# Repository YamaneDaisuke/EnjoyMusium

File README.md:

# EnjoyMusium
エンジョイ科学館で使用するプログラムや文書用リポジトリ

## フォルダ構成
 - **IR_Controller**
   赤外信号学習コントローラ用フォルダ
   - documents
   - PCB
   - programs
     - LPC1114 (LPC1114FN用プログラム 開発環境: mbedオンラインIDE)
     - PIC16F690.X  (PIC16F690用プログラム 開発環境: MPLAB X IDE)
 
 - **SpeechSynthesisWriter**
   音声合成回路用フォルダ
   - documents
   - PCB
   - programs
    - lpc1114fn (LPC1114FN用プログラム 開発環境: mbedオンラインIDE)
    - SetUp (インストーラ用プロジェクト 開発環境: visual studiio2015)
    - SpeechSynthesisWriter_CS (書き込みツール用プロジェクト 開発環境: visual studiio2015)

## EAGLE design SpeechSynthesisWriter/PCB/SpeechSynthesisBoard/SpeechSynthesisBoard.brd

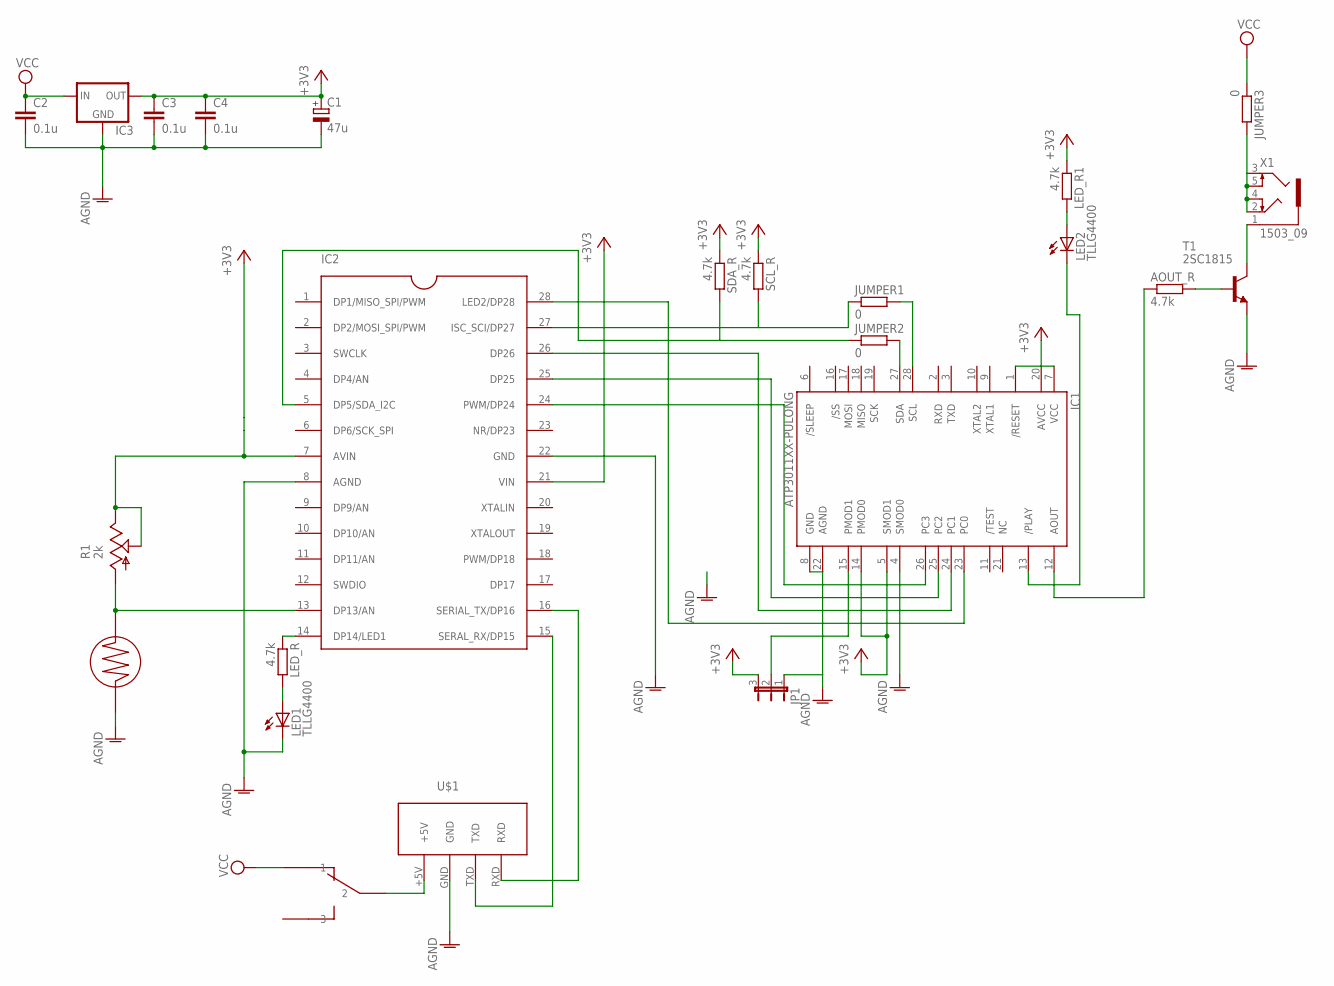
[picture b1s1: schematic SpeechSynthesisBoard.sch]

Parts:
AOUT_R: 4.7k; 0204/7
B-12JB1: B-12JV
C1: 47u; E2,5-5
C2, C3, C4: 0.1u; C025-024X044
CDS_5MM1: CDS_5MM
IC1: ATP3011XX-PULONG; DIL28-3
IC2: LPC1114FN28; DIP28
IC3: 78XXL
JP1: JP2E; JP2
JUMPER1, JUMPER2, JUMPER3: 0; 0309/12
LED1, LED2: TLLG4400; LED3MM
LED_R, LED_R1: 4.7k; 0204/7
R1: 2k; CA6V
SCL_R: 4.7k; 0204/7
SDA_R: 4.7k; 0204/7
T1: 2SC1815; TO92-ECB
U$1: USB2UART
X1: 1503_09

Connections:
+3V3: C1.+, C3.1, C4.1, IC1.1 (/RESET), IC1.5 (SMOD1), IC1.7 (VCC), IC1.14 (PMOD0), IC1.20 (AVCC), IC2.7 (AVIN), IC2.21 (VIN), IC3.OUT, JP1.3, LED_R1.1, R1.E, R1.S, SCL_R.1, SDA_R.1
AGND: C1.-, C2.2, C3.2, C4.2, CDS_5MM1.P$2, IC1.4 (SMOD0), IC1.8 (GND), IC1.22 (AGND), IC2.8 (AGND), IC2.22 (GND), IC3.GND, JP1.1, LED1.K (C), T1.E, U$1.GND
unnamed: LED1.A, LED_R.2
unnamed: IC1.13 (/PLAY), LED2.K (C)
unnamed: IC2.14 (DP14/LED1), LED_R.1
unnamed: LED2.A, LED_R1.2
unnamed: AOUT_R.1, IC1.12 (AOUT)
unnamed: AOUT_R.2, T1.B
unnamed: IC2.27 (ISC_SCI/DP27), JUMPER1.1, SCL_R.2
unnamed: IC2.5 (DP5/SDA_I2C), JUMPER2.1, SDA_R.2
unnamed: T1.C, X1.1
unnamed: IC1.26 (PC3), IC2.24 (PWM/DP24)
unnamed: IC1.25 (PC2), IC2.25 (DP25)
unnamed: IC1.23 (PC0), IC2.28 (LED2/DP28)
unnamed: IC1.24 (PC1), IC2.26 (DP26)
unnamed: IC2.16 (SERIAL_TX/DP16), U$1.RXD
unnamed: IC1.15 (PMOD1), JP1.2
unnamed: IC2.15 (SERAL_RX/DP15), U$1.TXD
unnamed: B-12JB1.2, U$1.+5V
unnamed: IC1.27 (SDA), JUMPER2.2
unnamed: CDS_5MM1.P$1, IC2.13 (DP13/AN), R1.A
unnamed: IC1.28 (SCL), JUMPER1.2
unnamed: JUMPER3.2, X1.2, X1.3, X1.4, X1.5
VCC: B-12JB1.1, C2.1, IC3.IN, JUMPER3.1

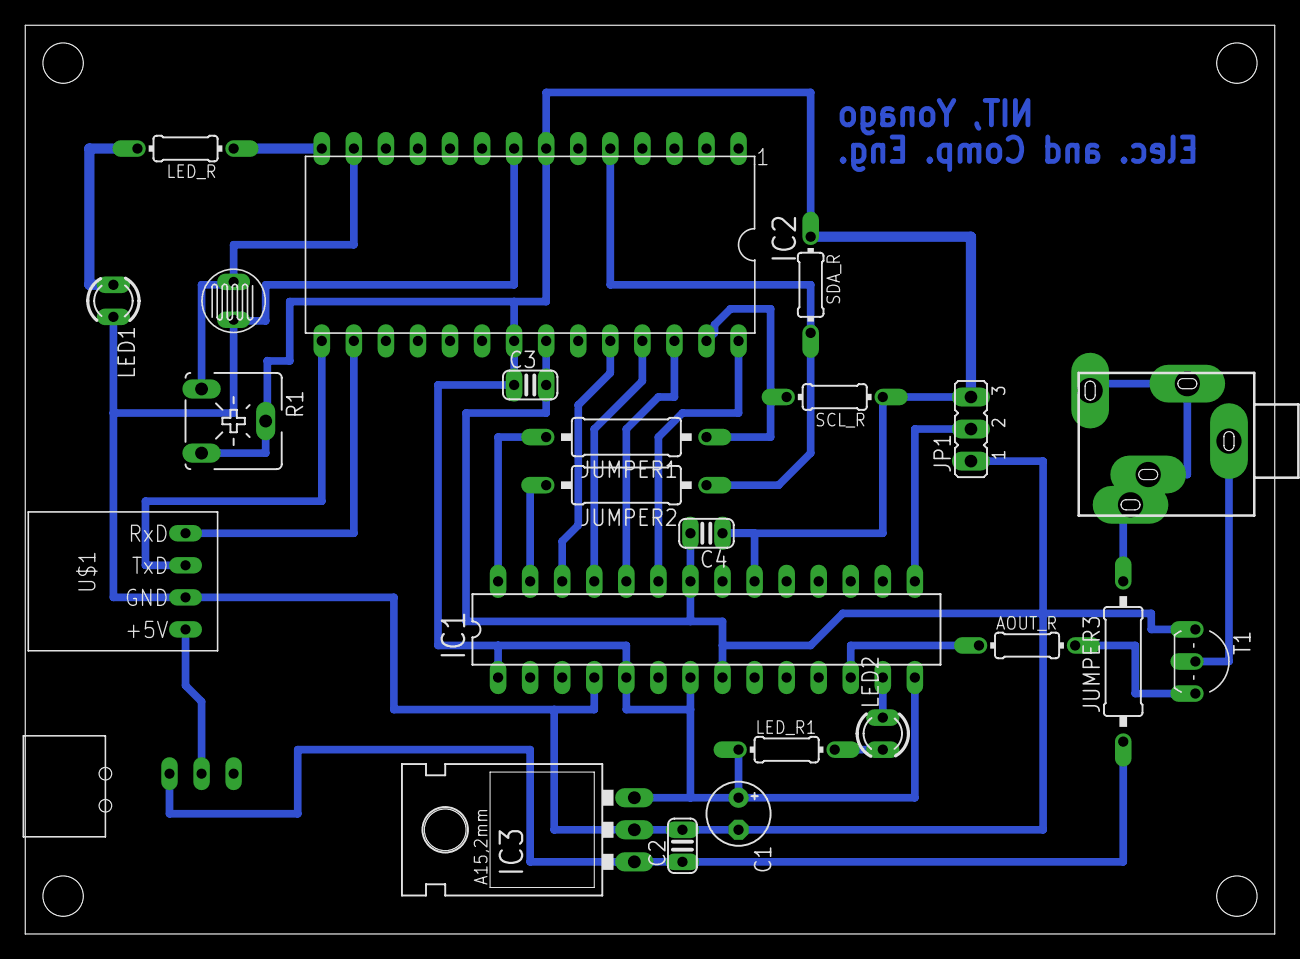
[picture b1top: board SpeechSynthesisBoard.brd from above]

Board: 2 copper layers, 99.0 x 72.0 mm, 24 parts (0 on the bottom side), 24 nets.

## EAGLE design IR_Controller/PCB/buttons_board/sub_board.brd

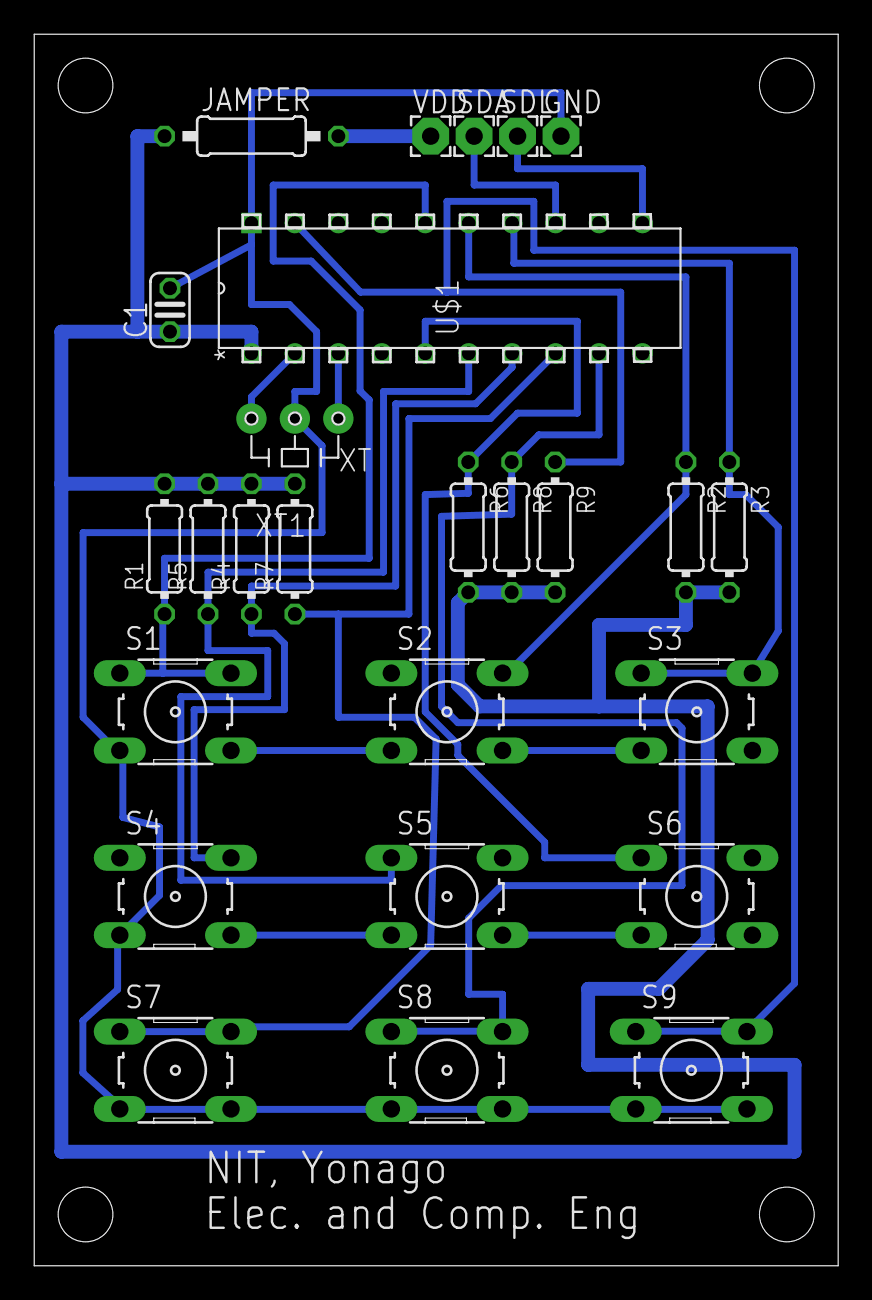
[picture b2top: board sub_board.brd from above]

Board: 2 copper layers, 47.0 x 72.0 mm, 26 parts (0 on the bottom side), 20 nets.

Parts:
C1: 0.1u; C025-024X044
GND: 2,15/1,0
JAMPER: 0; 0207/10
R1, R2, R3, R4, R5, R6, R7, R8, R9: 10k; 0204/7
S1, S2, S3, S4, S5, S6, S7, S8, S9: B3F-10XX
SDA: 2,15/1,0
SDL: 2,15/1,0
U$1: PIC16F690-X/P; PDIP20_300MC
VDD: 2,15/1,0
XT1: CERALOCK

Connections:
+3V3: C1.1, JAMPER.1, R1.2, R2.2, R3.2, R4.2, R5.2, R6.2, R7.2, R8.2, R9.2, U$1.P$1
GND: C1.2, GND.1, S1.3, S4.3, S7.3, S7.4, S8.3, S8.4, S9.3, S9.4, U$1.P$20, XT1.P$2
unnamed: R1.1, S1.1, S1.2, U$1.P$16
unnamed: R5.1, S5.1, U$1.P$6
unnamed: JAMPER.2, VDD.1
unnamed: R8.1, S8.1, S8.2, U$1.P$9
unnamed: R2.1, S2.2, U$1.P$15
unnamed: R3.1, S3.1, S3.2, U$1.P$14
unnamed: S4.4, S5.3
unnamed: S5.4, S6.3
unnamed: S1.4, S2.3
unnamed: R6.1, S6.1, U$1.P$5
unnamed: S2.4, S3.3
unnamed: U$1.P$3, XT1.P$1
unnamed: U$1.P$2, XT1.P$3
unnamed: SDA.1, U$1.P$13
unnamed: SDL.1, U$1.P$11
unnamed: R4.1, S4.2, U$1.P$7
unnamed: R9.1, S9.1, S9.2, U$1.P$19
unnamed: R7.1, S7.1, S7.2, U$1.P$8

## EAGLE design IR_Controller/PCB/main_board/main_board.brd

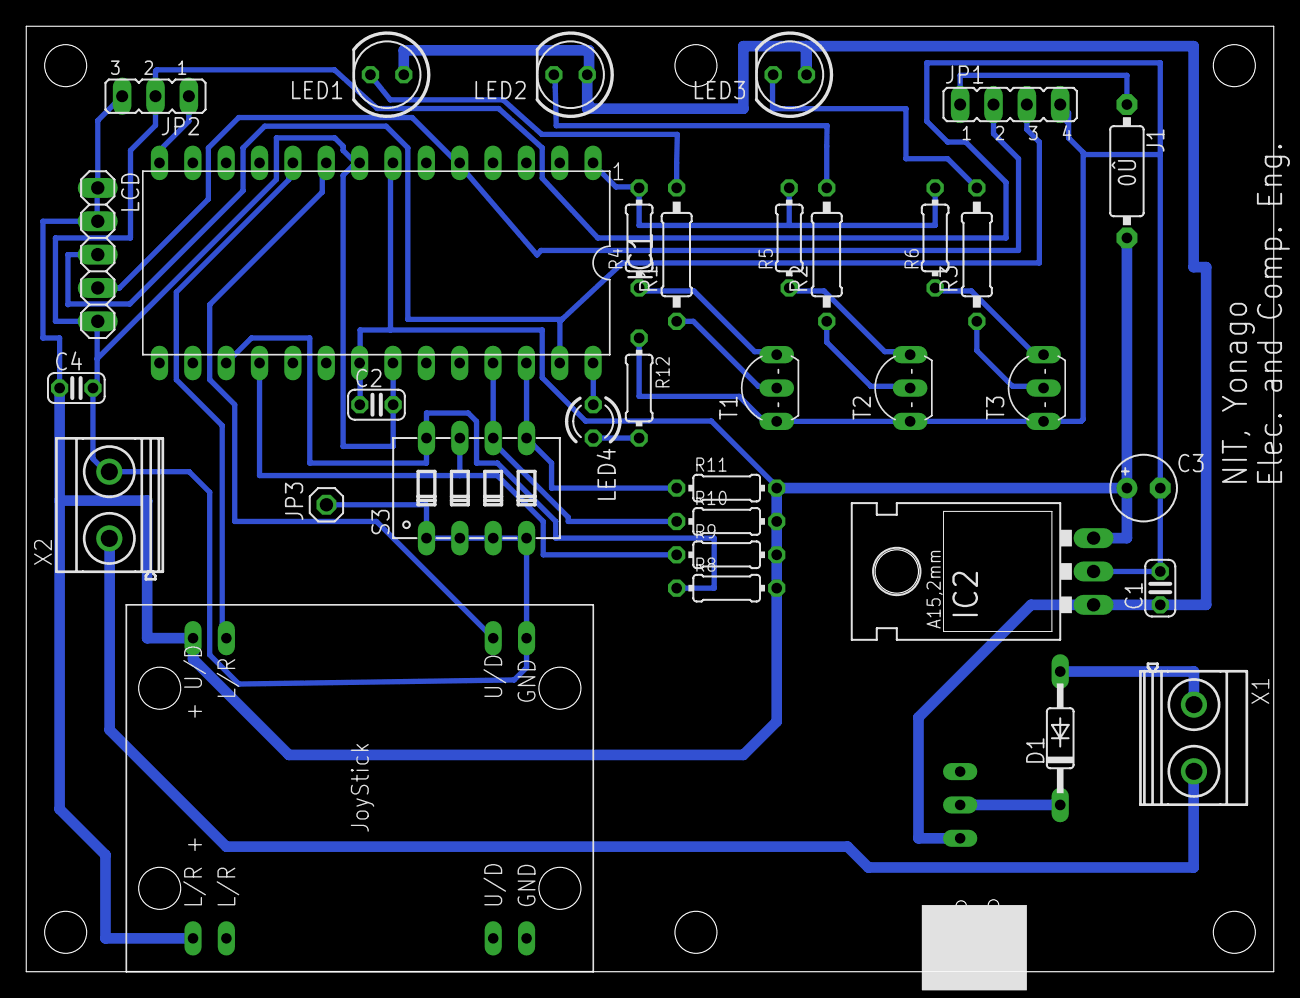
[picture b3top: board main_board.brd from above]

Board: 2 copper layers, 95.0 x 72.0 mm, 35 parts (0 on the bottom side), 28 nets.

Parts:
C1, C2, C4: 0.1u; C025-024X044
C3: 47u; E2,5-5
D1: BAT42; DO35-10
IC1: LPC1114FN28; DIP28
IC2: 78XXL
J1: 0R/10
JP1: JP4
JP2: JP2
JP3: 1X01
LCD: 1X05
LED1, LED2, LED3: LED5MM
LED4: LED3MM
R1, R2, R3: 110; 0207/10
R4, R5, R6, R8, R9, R10, R11, R12: 4.7k; 0204/7
S3: DIP04YL
T1, T2, T3: 2SC1815; TO92-ECB
U$1: ANALOGJOYSTICK; ANLOGJOYSTICK
U$2: TOGGLE-B-12JV
X1, X2: MKDSN1,5/2-5,08

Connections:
+3V3: C2.1, C3.+, C4.1, IC1.7, IC1.21, IC2.OUT, J1.2, JP2.3, LCD.1, LCD.2, R8.2, R9.2, R10.2, R11.2, U$1.R/L+, U$1.U/D+
+5V: C1.1, IC2.IN, LED1.A, LED2.A, LED3.A, U$2.P$1
GND: C1.2, C2.2, C3.-, C4.2, IC1.8, IC1.22, IC2.GND, JP1.4, JP2.2, JP3.1, LCD.5, R12.1, S3.1, S3.2, S3.3, S3.4, T1.E, T2.E, T3.E, U$1.GND2, X2.2
unnamed: R4.1, T1.B
unnamed: IC1.1, R4.2, R5.2, R6.2
unnamed: R5.1, T2.B
unnamed: R6.1, T3.B
unnamed: IC1.27, JP1.3, LCD.3
unnamed: LED2.K, R2.2
unnamed: LED1.K, R1.2
unnamed: LED3.K, R3.2
unnamed: R1.1, T1.C
unnamed: R2.1, T2.C
unnamed: R3.1, T3.C
unnamed: IC1.5, JP1.2, LCD.4
unnamed: IC1.14, JP2.1
unnamed: LED4.K, R12.2
unnamed: IC1.28, LED4.A
unnamed: IC1.17, R8.1, S3.8
unnamed: IC1.18, R9.1, S3.7
unnamed: IC1.25, R10.1, S3.6
unnamed: IC1.26, R11.1, S3.5
unnamed: IC1.10, U$1.L/R2
unnamed: IC1.9, U$1.U/D2
unnamed: X1.2, X2.1
unnamed: D1.A, X1.1
unnamed: D1.C, U$2.P$2
unnamed: J1.1, JP1.1

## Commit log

2016-07-01 First Commit!!
    IR_Controllerフォルダには、学習コントローラ絡みのプログラムや文書を
    SpeechSynthesisWriterフォルダには、音声合成回路絡みのものを配置
2016-07-01 READMEを編集
2016-07-06 lpc1114用ソースコード(人工音声)を追加
2016-07-14 ToDOリストを更新
2016-07-16 学習コントローラのドキュメントを編集
2016-07-16 人工音声のドキュメントを編集
2016-07-16 学習コントローラのプログラム(16f690用)を追加
2016-07-21 アイコンを追加
2016-07-21 mbedフォルダをlpc1114fnにリネーム
2016-07-21 書類を更新
2016-07-21 Update README.md
    フォルダ構成を追記
2017-02-24 add comment
2017-02-24 A4DVDケース用のテンプレートを追加
2017-04-06 rename PBC=>PCB
